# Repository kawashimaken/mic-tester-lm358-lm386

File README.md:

I use KiCad 6.0.1 for this project. All KiCad files are [here](https://github.com/kawashimaken/mic-tester-lm358-lm386/tree/main/mic_tester)

If you want to use PCB service, make sure you export your Gerberfile.

* V1.0 (KiCad 6.0.1) used in the video

* V1.1 (KiCad 6.0.5) not manufactured

# YouTube

# mic-tester-lm358-lm386

* This repo is for learning purpose!

* The [mic_tester](https://github.com/kawashimaken/mic-tester-lm358-lm386/tree/main/mic_tester) folder contains all files for KiCad.

* Feel free to play with it.

* It will be appriciated if you have any feedback or suggestions to improve it!

# Heavily inspired by the following article

* EC044T-R1
コンデンサーマイク（ECM)
チェッカー：http://www.or2.fiberbit.net/takehiko-inoue01/denshikousaku2013.html#_EC044T-R1

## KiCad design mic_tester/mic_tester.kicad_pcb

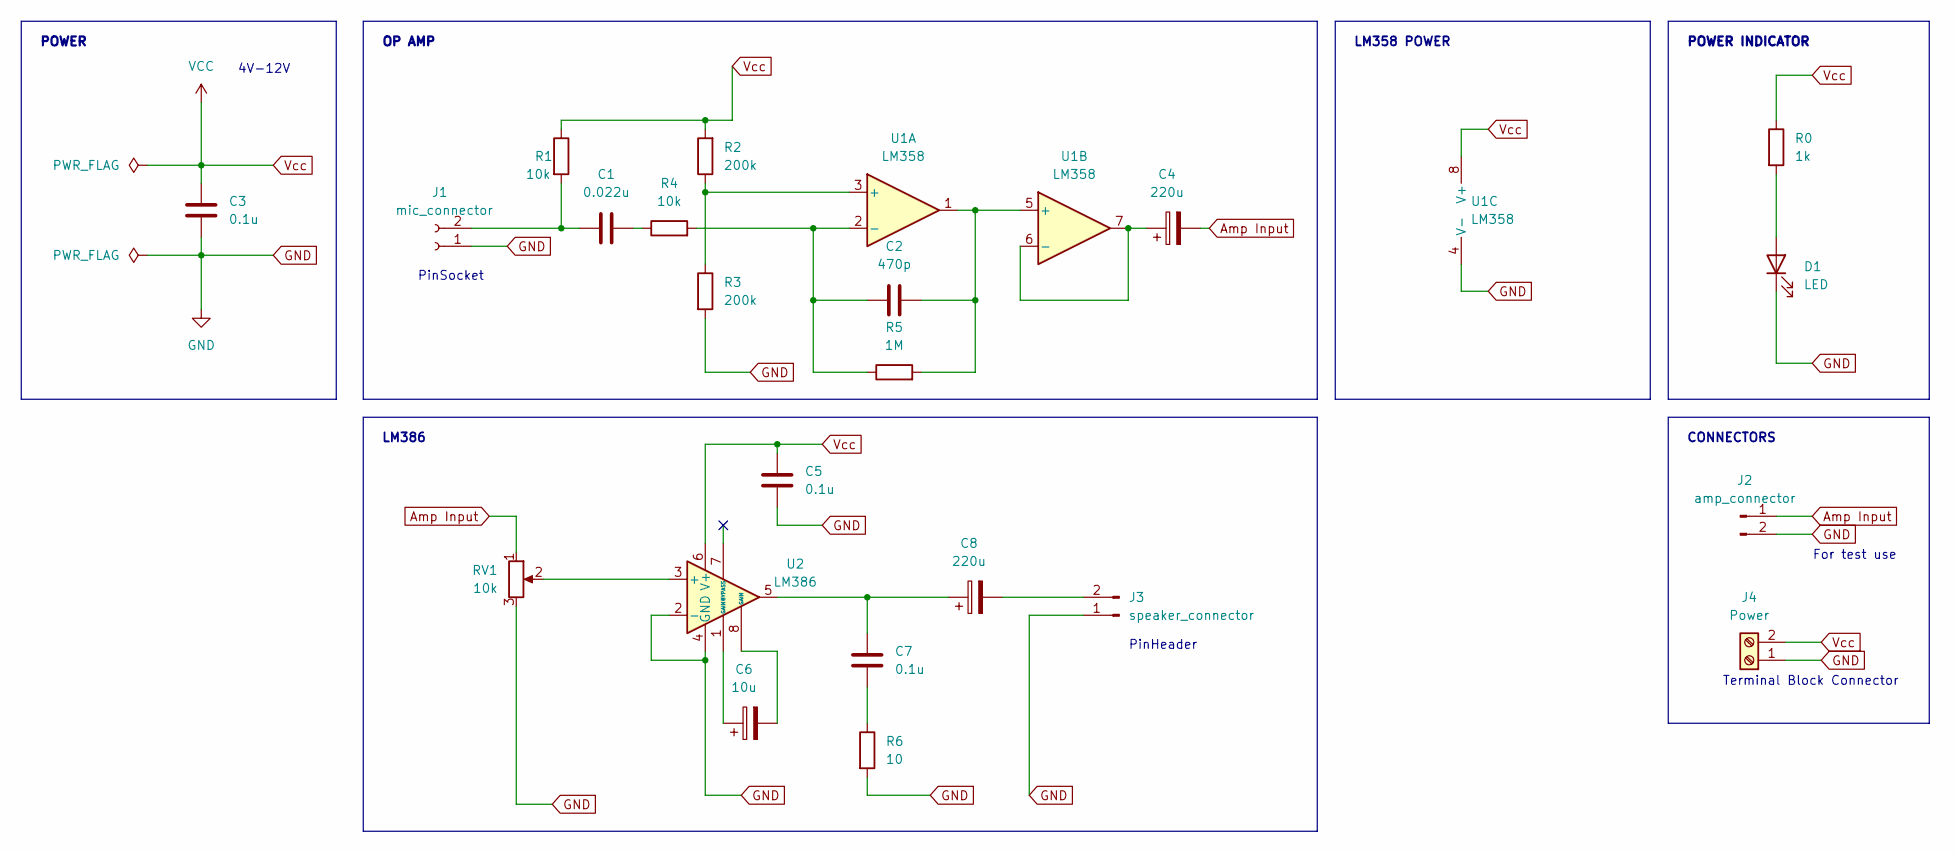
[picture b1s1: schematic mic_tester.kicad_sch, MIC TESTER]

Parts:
C1: 0.022u; C_Disc_D5.0mm_W2.5mm_P2.50mm
C2: 470p; C_Disc_D5.0mm_W2.5mm_P2.50mm
C3, C5, C7: 0.1u; C_Disc_D5.0mm_W2.5mm_P2.50mm
C4, C8: 220u; CP_Radial_D10.0mm_P2.50mm
C6: 10u; CP_Radial_D5.0mm_P2.50mm
D1: LED; LED_D5.0mm
J1: mic_connector; PinSocket_1x02_P2.54mm_Vertical
J2: amp_connector; PinHeader_1x02_P2.54mm_Vertical
J3: speaker_connector; PinHeader_1x02_P2.54mm_Vertical
J4: Power; TerminalBlock_Phoenix_MKDS-1,5-2-5.08_1x02_P5.08mm_Horizont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
R0: 1k; R_Axial_DIN0207_L6.3mm_D2.5mm_P10.16mm_Horizontal
R1, R4: 10k; R_Axial_DIN0207_L6.3mm_D2.5mm_P10.16mm_Horizontal
R2, R3: 200k; R_Axial_DIN0207_L6.3mm_D2.5mm_P10.16mm_Horizontal
R5: 1M; R_Axial_DIN0207_L6.3mm_D2.5mm_P10.16mm_Horizontal
R6: 10; R_Axial_DIN0207_L6.3mm_D2.5mm_P10.16mm_Horizontal
RV1: 10k; Potentiometer_Piher_PT-6-V_Vertical
U1: LM358; DIP-8_W7.62mm
U2: LM386; DIP-8_W7.62mm

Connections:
Amp Input: C4.2, J2.1, RV1.1
GND: C3.1, C5.2, D1.1 (K), J1.1, J2.2, J3.1, J4.1, R3.2, R6.2, RV1.3, U1.4 (V-), U2.2 (-), U2.4 (GND)
unnamed: C1.1, J1.2, R1.2
unnamed: C1.2, R4.1
unnamed: C2.1, R4.2, R5.1, U1.2 (-)
unnamed: C2.2, R5.2, U1.1, U1.5 (+)
unnamed: C4.1, U1.6 (-), U1.7
unnamed: C6.1, U2.1 (GAIN)
unnamed: C6.2, U2.8 (GAIN)
unnamed: C7.1, C8.1, U2.5
unnamed: C7.2, R6.1
unnamed: C8.2, J3.2
unnamed: D1.2 (A), R0.2
unnamed: R2.1, R3.1, U1.3 (+)
unnamed: RV1.2, U2.3 (+)
Vcc: C3.2, C5.1, J4.2, R0.1, R1.1, R2.2, U1.8 (V+), U2.6 (V+)

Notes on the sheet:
POWER INDICATOR
OP AMP
For test use
LM358 POWER
PinSocket
4V-12V
Terminal Block Connector
CONNECTORS
LM386
POWER
PinHeader

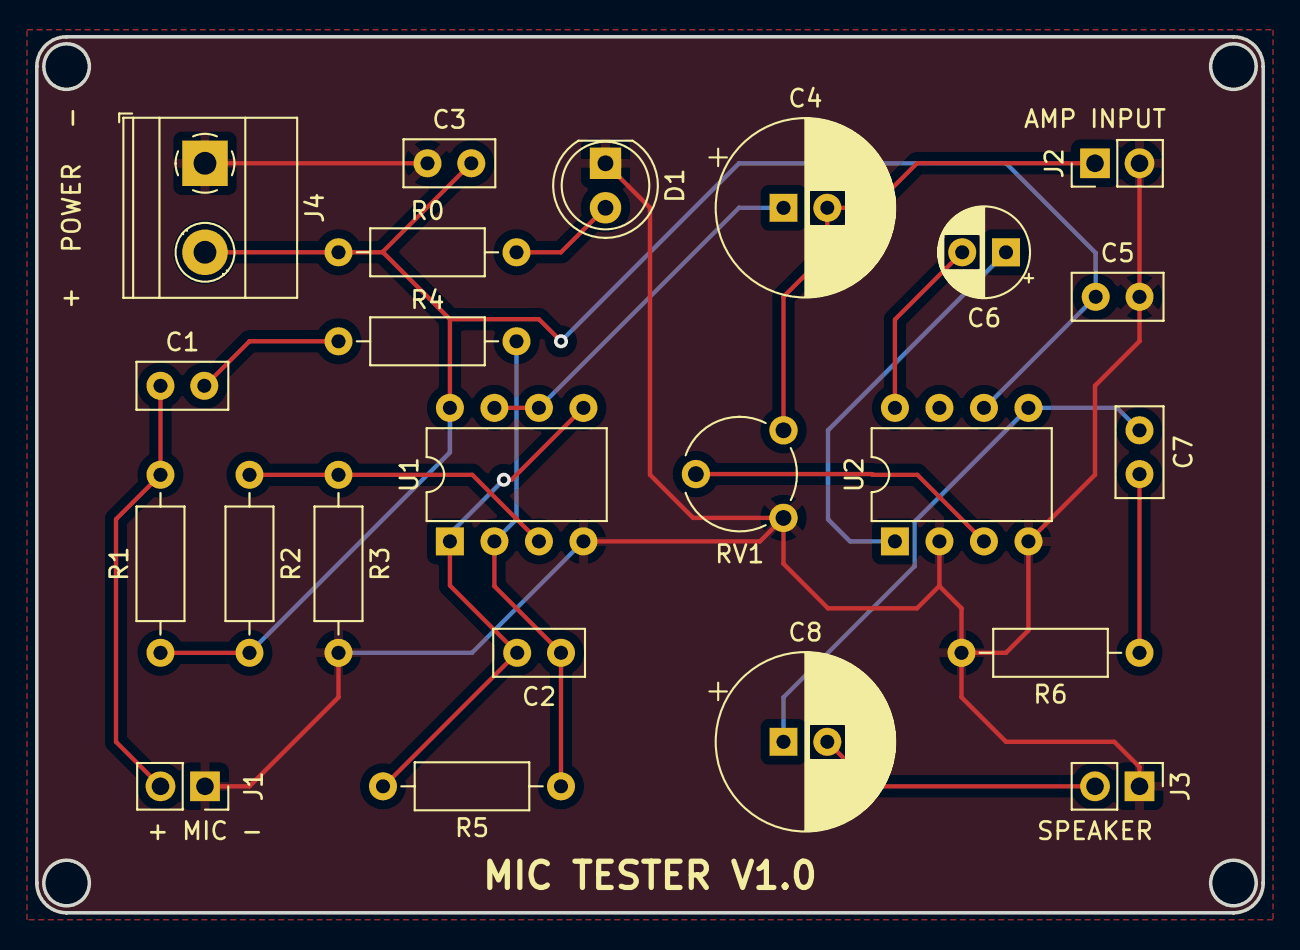
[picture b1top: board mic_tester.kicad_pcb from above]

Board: 2 copper layers, 70.0 x 50.0 mm, 23 parts (0 on the bottom side), 16 nets.

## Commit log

2022-04-28 init commit
2022-04-29 add pictures
2022-04-29 add text to schematics
2022-04-29 add ignore file
2022-04-29 add gitignore file
2022-05-03 fix error
2022-05-03 improve fix
2022-05-17 update files
